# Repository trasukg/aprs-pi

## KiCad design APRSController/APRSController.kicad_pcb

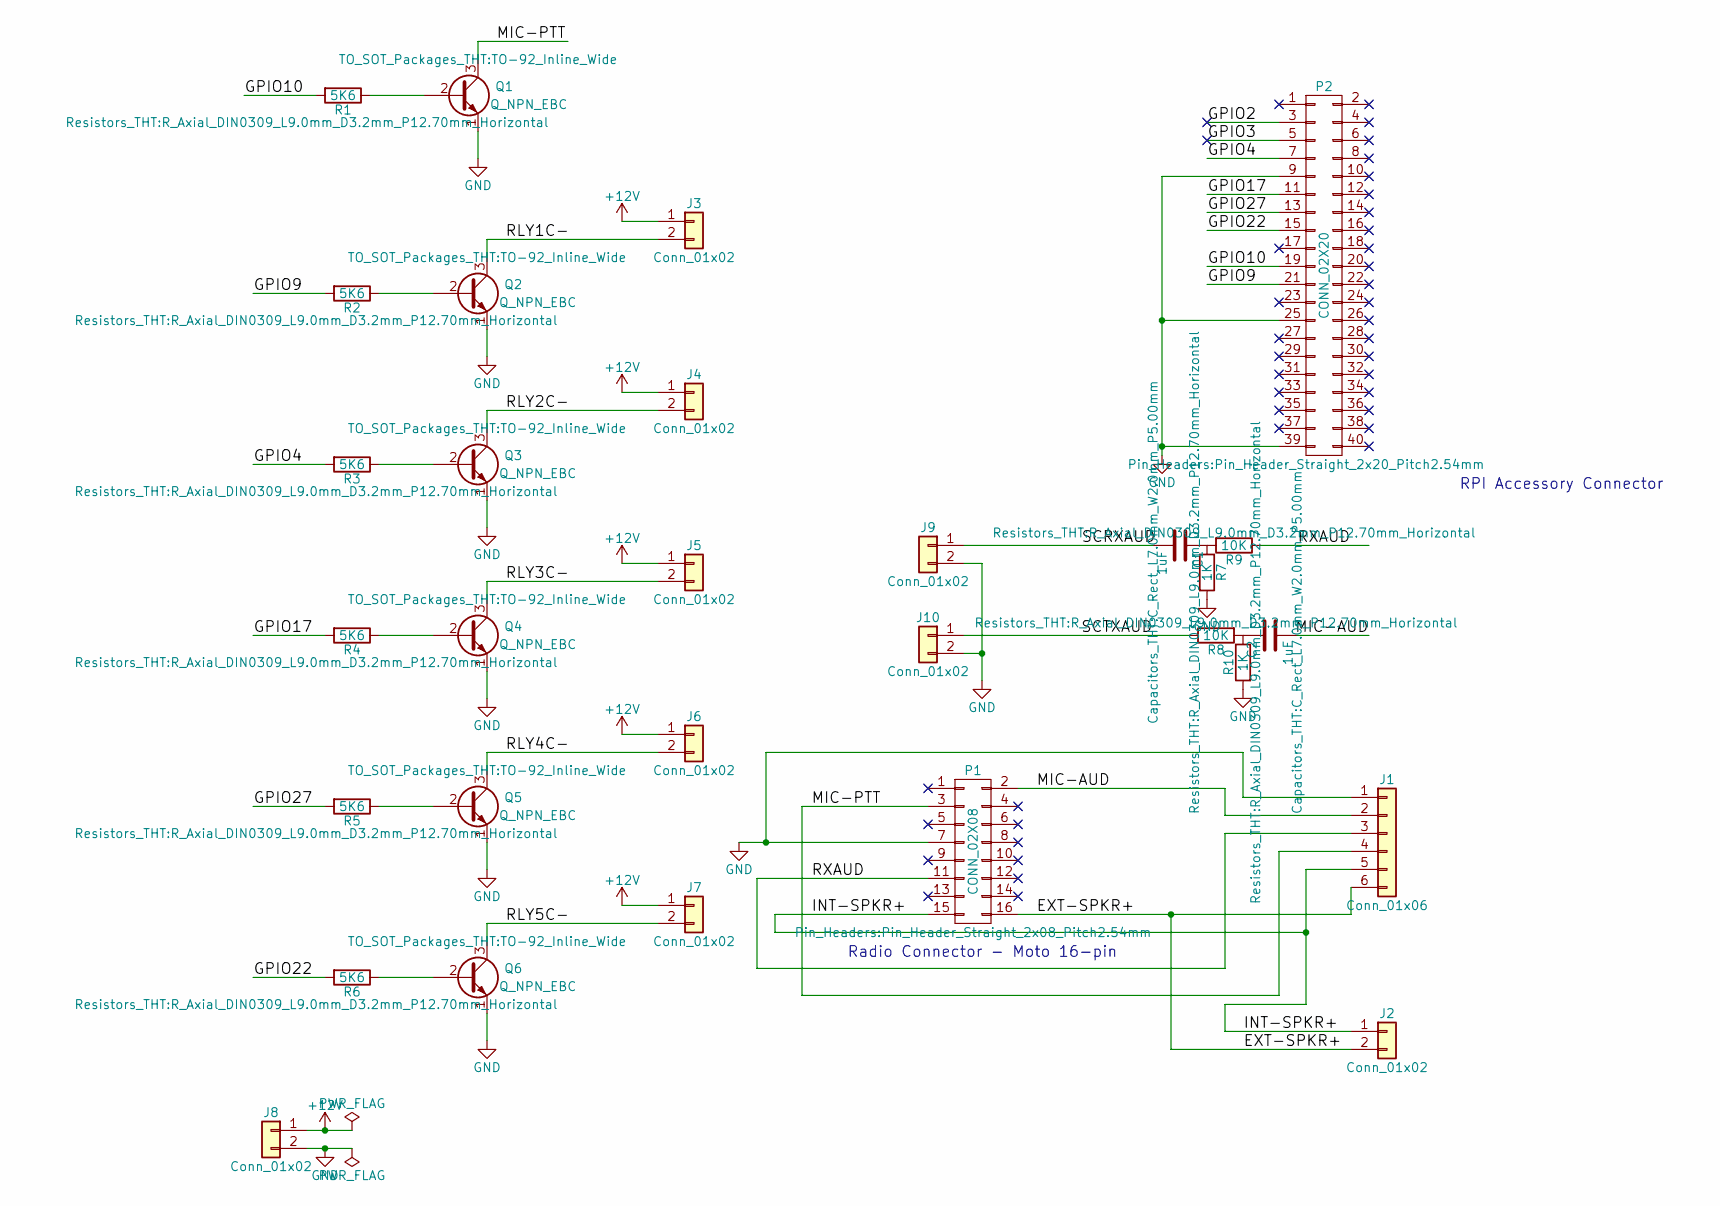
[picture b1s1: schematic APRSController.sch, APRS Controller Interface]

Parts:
C1, C2: 1uF; C_Rect_L7.0mm_W2.0mm_P5.00mm
J1: Conn_01x06; Molex_KK-6410-06_06x2.54mm_Straight
J2, J3, J4, J5, J6, J7, J8, J9, J10: Conn_01x02; Molex_KK-6410-02_02x2.54mm_Straight
P1: CONN_02X08; Pin_Header_Straight_2x08_Pitch2.54mm
P2: CONN_02X20; Pin_Header_Straight_2x20_Pitch2.54mm
Q1, Q2, Q3, Q4, Q5, Q6: Q_NPN_EBC; TO-92_Inline_Wide
R1, R2, R3, R4, R5, R6: 5K6; R_Axial_DIN0309_L9.0mm_D3.2mm_P12.70mm_Horizontal
R7, R10: 1K; R_Axial_DIN0309_L9.0mm_D3.2mm_P12.70mm_Horizontal
R8, R9: 10K; R_Axial_DIN0309_L9.0mm_D3.2mm_P12.70mm_Horizontal

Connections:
+12V: J3.1, J4.1, J5.1, J6.1, J7.1, J8.1
/EXT-SPKR+: J1.6, J2.2, P1.16
/GPIO2: P2.3
/GPIO3: P2.5
/GPIO4: P2.7, R3.2
/GPIO9: P2.21, R2.2
/GPIO10: P2.19, R1.2
/GPIO17: P2.11, R4.2
/GPIO22: P2.15, R6.2
/GPIO27: P2.13, R5.2
/INT-SPKR+: J1.5, J2.1, P1.15
/MIC-AUD: C2.2, J1.2, P1.2
/MIC-PTT: J1.4, P1.3, Q1.3 (C)
/RLY1C-: J3.2, Q2.3 (C)
/RLY2C-: J4.2, Q3.3 (C)
/RLY3C-: J5.2, Q4.3 (C)
/RLY4C-: J6.2, Q5.3 (C)
/RLY5C-: J7.2, Q6.3 (C)
/RXAUD: J1.3, P1.11, R9.1
/SCRXAUD: C1.2, J9.1
/SCTXAUD: J10.1, R8.1
GND: J1.1, J8.2, J9.2, J10.2, P1.7, P2.9, P2.25, P2.39, Q1.1 (E), Q2.1 (E), Q3.1 (E), Q4.1 (E), Q5.1 (E), Q6.1 (E), R7.2, R10.2
unnamed: C1.1, R7.1, R9.2
unnamed: C2.1, R8.2, R10.1
unnamed: Q1.2 (B), R1.1
unnamed: Q2.2 (B), R2.1
unnamed: Q3.2 (B), R3.1
unnamed: Q4.2 (B), R4.1
unnamed: Q5.2 (B), R5.1
unnamed: Q6.2 (B), R6.1

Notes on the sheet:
Radio Connector - Moto 16-pin
RPI Accessory Connector

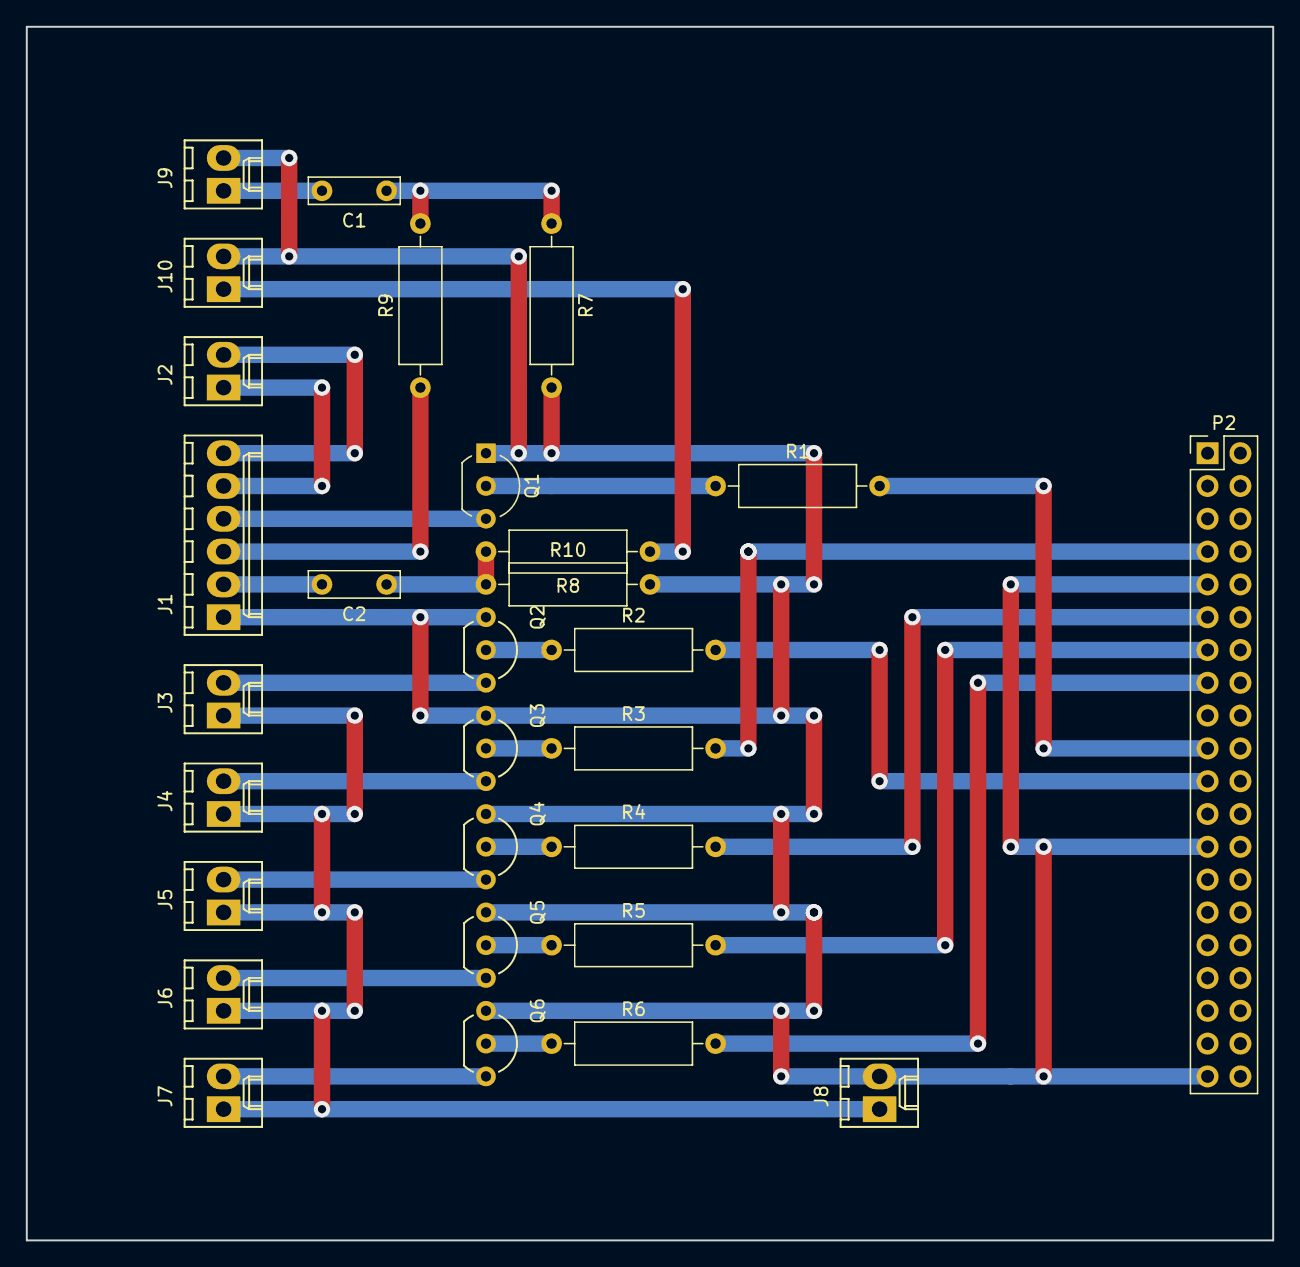
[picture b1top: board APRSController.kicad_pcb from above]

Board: 2 copper layers, 96.5 x 94.0 mm, 29 parts (0 on the bottom side), 28 nets.

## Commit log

2018-01-14 First commit.
2018-01-21 Initial pass at test and calibration programs.
2018-01-25 Added toggleptt.py
2018-01-25 Added gpio cleanup call on exit
2018-01-31 Changed ptt gpio to be GPIO10, as per revised circuit design.
2018-01-31 Changed controller circuit so as to avoid the I2C lines on the Pi. PTT is now GPIO10. First output is now GPIO9.
    Added two-tone calibration audio to manual test package.
2018-01-31 Make the calibration audio stereo.
2018-02-01 Modified APRSController to use GPIO10 and GPIO9 rather than GPIO2 and GPIO3
2020-10-17 Modifications for the BARC digipeater.
